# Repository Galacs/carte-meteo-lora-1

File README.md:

# Carte Meteo Lora 1

Solar and battery powered LoRa weather station

## IC List

- STM32L431CCT6 (Low power MCU)
- HT7150 (+3V3 LDO)
- SX1262TR8 (SX1262 LoRa module)
- WS2812B (Addressable RGB LED)
- MS5607 (Pressure sensor)
- GXHT30 (Humidity and temperature sensor)
- HTU21D (Humidity and temperature sensor)
- BQ25798 (1s battery charger with MPPT)
- TPS6282 (SMPS)

## Top preview

## Preview 3d render

## Pictures

## Pin definitions

```c
#define LORA_RST_PIN PB0
#define LORA_DIO1_PIN PB1
#define LORA_BUSY_PIN PB11
#define LORA_DIO3_PIN PB10
#define LORA_CS_PIN PA4
#define LORA_SCK_PIN PA5
#define LORA_MISO_PIN PA6
#define LORA_MOSI PA7

#define BTN_PIN PB12
#define STATUS_PIN PB13

#define SCL_PIN PB6
#define SDA_PIN PB7
#define CE_PIN PA11
#define INT_PIN PA12
#define QON_PIN PA10

#define RGB_PIN PC13

#define RAIN_PIN PB4
#define W_DIR_PIN PA1
#define WIND_PIN PA0
```

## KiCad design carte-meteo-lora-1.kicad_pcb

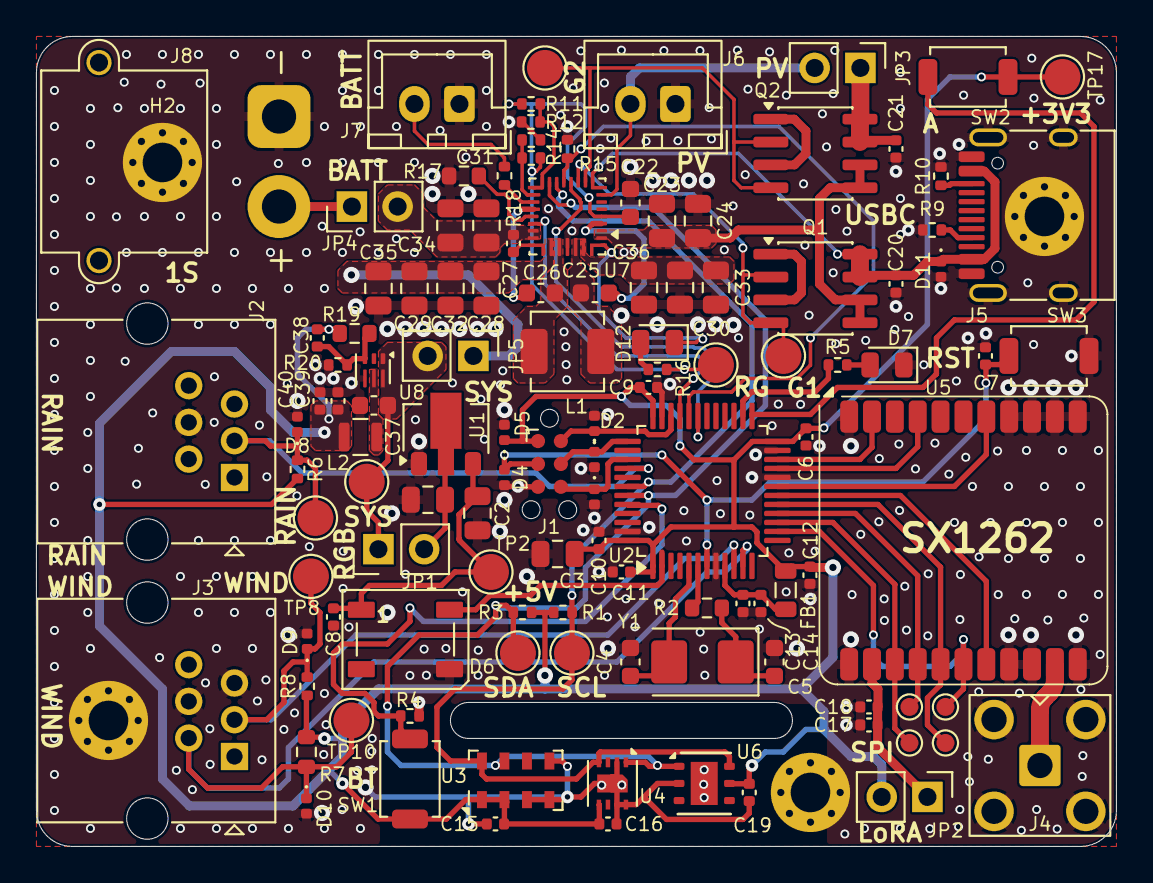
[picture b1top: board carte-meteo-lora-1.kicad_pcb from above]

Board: 2 copper layers, 60.0 x 45.0 mm, 121 parts (0 on the bottom side), 60 nets.

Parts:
C1, C2, C3, C23, C24, C28, C29, C30, C31, C32, C33, C34, C35, C36: 10u; C_0805_2012Metric
C4, C5: 20p; C_0603_1608Metric
C6, C7, C9, C10, C11, C15, C16, C18, C19, C20, C21: 0u1; C_0402_1005Metric
C8, C12, C13: 1u; C_0402_1005Metric
C14: 10n; C_0402_1005Metric
C17, C39, C40: 10u; C_0402_1005Metric
C22: 4u7; C_0603_1608Metric
C25, C26: 47n; C_0603_1608Metric
C27: 1n; C_0402_1005Metric
C37: 10u; C_0603_1608Metric
C38: 100p; C_0402_1005Metric
D1, D2, D3, D4, D5, D8, D9, D10, D11: H5VU10U; Diode_DFN1006
D6: WS2812B; LED_WS2812B_PLCC4_5.0x5.0mm_P3.2mm
D7: YELLOW; LED_0805_2012Metric
D12: GREEN; LED_0805_2012Metric
FB1: 600Ω@100M; L_0805_2012Metric
H1, H2, H3, H4: MountingHole_Pad; MountingHole_2.2mm_M2_Pad_Via
J1: TC2030; Tag-Connect_TC2030-IDC-NL_2x03_P1.27mm_Vertical
J2, J3: Conn_01x04; RJ25_Wayconn_MJEA-660X1_Horizontal
J4: Conn_Coaxial; SMA_BAT_Wireless_BWSMA-KWE-Z001
J5: USB_C_Receptacle_USB2.0_14P; USB_C_Receptacle_HRO_TYPE-C-31-M-12
J6: Solar_Cell; JST_XH_B2B-XH-A_1x02_P2.50mm_Vertical
J7: Conn_01x02; JST_XH_B2B-XH-A_1x02_P2.50mm_Vertical
J8: Battery_Cell; AMASS_XT30PW-M_1x02_P2.50mm_Horizontal
JP1, JP2, JP3, JP4, JP5: Jumper_2_Small_Bridged; PinHeader_1x02_P2.54mm_Vertical
L1: 1u; L_Changjiang_FXL0420
L2: 0u47; TDK_TFM201610ALC
Q1, Q2: AO4882; SOIC-8_3.9x4.9mm_P1.27mm
R1, R3, R4, R6, R8, R11, R12, R15: 10k; R_0402_1005Metric
R2: 560; R_0603_1608Metric
R5, R9, R10, R16: 5k1; R_0402_1005Metric
R7: 470k; R_0603_1608Metric
R13, R20: 100k; R_0402_1005Metric
R14: 52k3; R_0402_1005Metric
R17: 3k; R_0603_1608Metric
R18: 100; R_0402_1005Metric
R19: 430k; R_0603_1608Metric
SW1, SW2, SW3: SW_Push; SW_SPST_TS-1088-xR020
TP1, TP2, TP3, TP4, TP6, TP8, TP10, TP13, TP14, TP15, TP17: TestPoint; TestPoint_Pad_D2.0mm
TP7, TP9, TP11, TP12: TestPoint; TestPoint_Pad_D1.0mm
U1: HT7150-1; SOT-89-3
U2: STM32L431CCTx; LQFP-48_7x7mm_P0.5mm
U3: MS5607-02BA; LGA-8_3x5mm_P1.25mm
U4: GXHT30; Sensirion_DFN-8-1EP_2.5x2.5mm_P0.5mm_EP1.1x1.7mm
U5: SX1262TR8-GC; Silicontra_SX1262ZTR8
U6: HTU21; Texas_PWSON-N6
U7: BQ25798; Texas_RQM0029A_VQFN-29_4x4mm_P0.4mm
U8: TPS6282x; Texas_VSON-6_1.5x1.5mm_P0.5mm_DMQ0006A
Y1: 8M; Crystal_SMD_5032-2Pin_5.0x3.2mm

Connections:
+3V3: C3.1, C6.1, C9.1, C10.1, C11.1, C12.1, C15.2, C16.2, C17.1, C18.2, C19.2, C38.1, C39.1, C40.1, D5.1 (K), FB1.2, J1.1 (VCC), JP2.1 (A), JP2.2 (B), L2.2, R1.2, R3.1, R6.2, R7.1, R8.1, R19.1, SW1.1, SW2.1, TP17.1 (1_1), U2.1 (VBAT), U2.24 (VDD), U2.36 (VDD), U2.48 (VDD), U3.1 (VDD), U3.2 (PS), U4.5 (VDD), U5.13 (VCC), U6.5 (VCC)
+5V: C2.1, C8.1, D6.1 (VDD), TP2.1 (1_1), U1.3 (VOUT)
+REGN: C22.1, R11.1, R13.1, R16.2, TP15.1 (1_1), U7.5 (REGN)
+SYS: C1.1, C28.1, C29.1, C32.1, C35.1, C37.1, JP1.1 (A), JP1.2 (B), JP5.1 (A), JP5.2 (B), TP1.1 (1_1), U1.2 (VIN), U7.25 (SYS), U8.1 (EN), U8.6 (VIN)
+Vbus: C20.1, D11.1 (K), J5.A4 (VBUS), J5.A9 (VBUS), J5.B4 (VBUS), J5.B9 (VBUS), Q1.7 (D1), Q1.8 (D1), U7.9 (VAC1)
/BOOT: R4.2, SW1.2, U2.44 (PH3)
/BTN1: SW2.2, U2.25 (PB12)
/BUSY: U2.22 (PB11), U5.10 (BUSY)
/CS: TP9.1 (1_1), U2.14 (SPI1_NSS), U5.17 (CS)
/DIO1: U2.19 (PB1), U5.5 (DIO1)
/DIO3: U2.21 (PB10), U5.8 (DIO3)
/MISO: TP11.1 (1_1), U2.16 (SPI1_MISO), U5.15 (MISO)
/MOSI: TP12.1 (1_1), U2.17 (SPI1_MOSI), U5.16 (MOSI)
/NRST: C7.2, D4.1 (K), J1.3 (~RESET), SW3.2, U2.7 (NRST)
/Power/~CE: R15.2, U2.32 (PA11), U7.13 (~CE)
/Power/~INT: U2.33 (PA12), U7.21 (~INT)
/Power/~QON: U2.31 (PA10), U7.12 (~QON)
/RAIN: D8.1 (K), J2.3, R6.1, TP6.1 (1_1), U2.40 (PB4)
/RF_LR: J4.1 (In), U5.21 (ANT)
/RGB1: D6.4 (DIN), U2.2 (PC13)
/RST: U2.18 (PB0), U5.18 (RST)
/SCK: TP7.1 (1_1), U2.15 (SPI1_SCK), U5.14 (SCK)
/SCL: R1.1, TP3.1 (1_1), U2.42 (I2C1_SCL), U3.8 (SCLK), U4.4 (SCL), U6.6 (SCL), U7.14 (SCL)
/SDA: R3.2, TP4.1 (1_1), U2.43 (I2C1_SDA), U3.7 (SDI/SDA), U4.1 (SDA), U6.1 (SDA), U7.15 (SDA)
/SWCLK: D3.1 (K), J1.4 (SWCLK), U2.37 (SWCLK)
/SWDIO: D2.1 (K), J1.2 (SWDIO), U2.34 (IR_OUT)
/SWO: D1.1 (K), J1.6 (SWO), U2.39 (SWO)
/WIND: D9.1 (K), J3.3, R8.2, TP8.1 (1_1), U2.10 (PA0)
/W_DIR: D10.1 (K), J3.2, R7.2, TP10.1 (1_1), U2.11 (ADC1_IN6)
/XTAL_I: C4.1, U2.5 (RCC_OSC_IN), Y1.2
/XTAL_O: R2.2, U2.6 (RCC_OSC_OUT)
/XTAL_RO: C5.1, R2.1, Y1.1
GND: C1.2, C2.2, C3.2, C4.2, C5.2, C6.2, C7.1, C8.2, C9.2, C10.2, C11.2, C12.2, C13.2, C14.2, C15.1, C16.1, C17.2, C18.1, C19.1, C20.2, C21.2, C22.2, C23.2, C24.2, C28.2, C29.2, C30.2, C31.2, C32.2, C33.2, C34.2, C35.2, C36.2, C37.2, C39.2, C40.2, D1.2 (A), D2.2 (A), D3.2 (A), D4.2 (A), D5.2 (A), D6.3 (VSS), D7.1 (K), D8.2 (A), D9.2 (A), D10.2 (A), D11.2 (A), H1.1 (1_1), H2.1 (1_1), H3.1 (1_1), H4.1 (1_1), J1.5 (GND), J2.4, J3.4, J3.5, J4.2 (Ext), J5.A1 (GND), J5.A12 (GND), J5.B1 (GND), J5.B12 (GND), J5.SH (SHIELD), J6.1 (+), J7.1, J8.1 (+), R4.1, R9.1, R10.1, R12.1, R14.1, R15.1, R17.2, R20.2, SW3.1, U1.1 (GND), U2.8 (VSSA), U2.20 (PB2), U2.23 (VSS), U2.35 (VSS), U2.47 (VSS), U3.3 (GND), U3.4 (CSB), U3.5 (CSB), U4.2 (ADDR), U4.7 (R), U4.8 (VSS), U4.9 (VSS), U5.1 (GND), U5.2 (GND), U5.3 (GND), U5.4 (GND), U5.11 (GND), U5.12 (GND), U5.19 (GND), U5.20 (GND), U5.22 (GND), U6.2 (GND), U7.27 (GND), U8.4 (GND)
unnamed: C23.1, C24.1, Q1.5 (D2), Q1.6 (D2), Q2.5 (D2), Q2.6 (D2), U7.2 (VBUS), U7.3 (VBUS)
unnamed: D7.2 (A), R5.2
unnamed: D12.2 (A), R16.1
unnamed: D12.1 (K), U7.1 (STAT)
unnamed: J5.A5 (CC1), R9.2
unnamed: J5.B5 (CC2), R10.2
unnamed: C21.1, J6.2 (-), JP3.1 (A), JP3.2 (B), Q2.7 (D1), Q2.8 (D1), U7.8 (VAC2)
unnamed: J7.2, R18.1
unnamed: C27.2, C31.1, C34.1, J8.2 (-), JP4.1 (A), JP4.2 (B), U7.22 (BAT), U7.23 (BAT)
unnamed: Q1.2 (G1), Q1.4 (G2), TP13.1 (1_1), U7.11 (ACDRV1)
unnamed: Q1.1 (S1), Q1.3 (S2)
unnamed: Q2.2 (G1), Q2.4 (G2), TP14.1 (1_1), U7.10 (ACDRV2)
unnamed: Q2.1 (S1), Q2.3 (S2)
unnamed: R5.1, U2.26 (PB13)
unnamed: C13.1, C14.1, FB1.1, U2.9 (VDDA)
unnamed: R18.2, U7.18 (BATP)
unnamed: C25.1, U7.4 (BTST1)
unnamed: C26.1, U7.19 (BTST2)
unnamed: R13.2, R14.2, U7.17 (ILIM_HIZ)
unnamed: C30.1, C33.1, C36.1, U7.29 (PMID)
unnamed: R17.1, U7.20 (PROG)
unnamed: C27.1, U7.24 (SDRV)
unnamed: C25.2, L1.1, U7.28 (SW1)
unnamed: C26.2, L1.2, U7.26 (SW2)
unnamed: R11.2, R12.2, U7.16 (TS)
unnamed: C38.2, R19.2, R20.1, U8.3 (FB)
unnamed: L2.1, U8.5 (SW)

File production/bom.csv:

Designator,Footprint,Quantity,Value,LCSC Part #
"C1, C2, C23, C24, C28, C29, C3, C30, C31, C32, C33, C34, C35, C36",0805,14,10u,C440198
"C10, C11, C15, C16, C18, C19, C20, C21, C6, C7, C9",0402,11,0u1,C307331
"C12, C13, C8",0402,3,1u,C52923
C14,0402,1,10n,C15195
"C17, C39, C40",0402,3,10u,C15525
C22,0603,1,4u7,C19666
"C25, C26",0603,2,47n,C1622
C27,0402,1,1n,C1523
C37,0603,1,10u,C19702
C38,0402,1,100p,C1546
"C4, C5",0603,2,20p,C1648
"D1, D10, D11, D2, D3, D4, D5, D8, D9",Diode_DFN1006,9,H5VU10U,C22395519
D12,0805,1,GREEN,C2297
D6,LED_WS2812B_PLCC4_5.0x5.0mm_P3.2mm,1,WS2812B,C2874885
D7,0805,1,YELLOW,C2296
FB1,0805,1,600Ω@100M,C81034
"J2, J3",RJ25_Wayconn_MJEA-660X1_Horizontal,2,Conn_01x04,C189750
J4,SMA_BAT_Wireless_BWSMA-KWE-Z001,1,Conn_Coaxial,C496551
J5,USB_C_Receptacle_HRO_TYPE-C-31-M-12,1,USB_C_Receptacle_USB2.0_14P,C393939
J6,JST_XH_B2B-XH-A_1x02_P2.50mm_Vertical,1,Solar_Cell,C158012
J7,JST_XH_B2B-XH-A_1x02_P2.50mm_Vertical,1,Conn_01x02,C158012
J8,AMASS_XT30PW-M_1x02_P2.50mm_Horizontal,1,Battery_Cell,C431092
"JP1, JP2, JP3, JP4, JP5",PinHeader_1x02_P2.54mm_Vertical,5,Jumper_2_Small_Bridged,
L1,L_Changjiang_FXL0420,1,1u,C167203
L2,TDK_TFM201610ALC,1,0u47,C2045043
"Q1, Q2",SOIC-8_3.9x4.9mm_P1.27mm,2,AO4882,C3040598
"R1, R11, R12, R15, R3, R4, R6, R8",0402,8,10k,C25744
"R10, R16, R5, R9",0402,4,5k1,C25905
"R13, R20",0402,2,100k,C25741
R14,0402,1,52k3,C26982
R17,0603,1,3k,C4211
R18,0402,1,100,C25076
R19,0603,1,430k,C25969
R2,0603,1,560,C23204
R7,0603,1,470k,C23178
"SW1, SW2, SW3",SW_SPST_TS-1088-xR020,3,SW_Push,C720477
TP4,TestPoint_Pad_D2.0mm,1,TestPoint,
U1,SOT-89-3,1,HT7150-1,C347184
U2,LQFP-48_7x7mm_P0.5mm,1,STM32L431CCTx,C486681
U3,LGA-8_3x5mm_P1.25mm,1,MS5607-02BA,C97627
U4,Sensirion_DFN-8-1EP_2.5x2.5mm_P0.5mm_EP1.1x1.7mm,1,GXHT30,C2913569
U5,Silicontra_SX1262ZTR8,1,SX1262TR8-GC,C42381682
U6,Texas_PWSON-N6,1,HTU21,C83479
U7,Texas_RQM0029A_VQFN-29_4x4mm_P0.4mm,1,BQ25798,C2876593
U8,Texas_VSON-6_1.5x1.5mm_P0.5mm_DMQ0006A,1,TPS6282x,C2650334
Y1,Crystal_SMD_5032-2Pin_5.0x3.2mm,1,8M,C115962

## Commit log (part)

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2026-05-19 remove TMP117 temp sensor
2026-05-19 schem: add MS5607 Pressure sensor
2026-05-20 schem: remove old gpios
2026-05-20 schem: add esp32-c5 with decoupling caps
2026-05-20 schem: replace esp32-s3 with esp32-c5
2026-05-20 schem: add GXHT30 humidity and temperature sensor
2026-05-20 schem: add HTU21 humidity and temperature
2026-05-20 schem: add wind and rain connectors
2026-05-20 schem: add SX1262 based lora module
2026-05-21 schem: add ordering info to BOM
2026-05-21 schem: fix BOM
2026-05-24 schem: add esp rf matching networks
2026-05-24 schem: reorganize
2026-05-24 schem: add TPS62933 5V SMPS
2026-05-24 schem: rf fix switchable connectors orientation
2026-05-24 schem: fix VDD_SPI cap
2026-05-24 schem: improve rain and wind connectors
2026-05-24 schem: add rain/wind schmitt trigger
2026-05-25 schem: remove 3s BMS
2026-05-25 schem: add BQ25798 MPPT/Charger/Protection/Boost
2026-05-25 schem: add TPS6282 3.3v SMPS
2026-05-25 schem: remove esp32
2026-05-25 schem: add STM32F103C8Tx
2026-05-25 schem: add usbc pwer connector
2026-05-25 schem: remove oled display
2026-05-25 schem: add HT7150-1 5V LDO for rgb led
2026-05-25 schem: connect gpios
2026-05-26 schem: change mcu to stm32l4
2026-05-26 schem: connect gpios to mcu
2026-05-26 schem: add current measure jumpers
2026-05-26 schem: add no connects
2026-05-26 schem: add test points
2026-05-26 schem: run and fix ERC
2026-05-26 schem: add net classes
2026-05-26 schem: assign footprints
2026-05-26 schem: add title
2026-05-26 schem: renumber
2026-05-26 pcb: import jlc 2 layer stackup
2026-05-26 pcb: add missing 3d models
2026-05-27 pcb: initial partitioning
2026-05-29 schem: add title to other sheet
2026-05-29 pcb: add missing lora 3d model
2026-05-29 pcb: add usb layout
2026-05-29 pcb: add solar charger layout
2026-05-29 pcb: add rgb led routing
2026-05-29 pcb: add smps routing
2026-05-29 pcb: add wind/rain connectors layout
2026-05-29 pcb: add sensors layout
2026-05-29 pcb: add lora layout
2026-05-29 pcb: add stm32 layout
2026-05-29 pcb: add board outline and final placement
2026-05-29 schem: add mounting holes
2026-05-29 pcb: add gnd planes
2026-05-29 pcb: add gnd vias
2026-05-29 pcb: add grid/place origin
2026-05-29 pcb: reorganize programmable gpios
2026-05-29 pcb: add rf routing
2026-05-29 pcb: add xtal routing
2026-05-29 pcb: add swd routing
2026-05-29 pcb: add i2c routing
2026-05-29 pcb: add solar charger routing
2026-05-29 pcb: add lora spi routing
2026-05-29 pcb: add rain/wind connectors routing
2026-05-29 pcb: add smps and +5v pwr routing
2026-05-29 pcb: add lora gpio routing
2026-05-29 pcb: add boot/rst routing
2026-05-29 pcb: connect charger to mcu
2026-05-29 pcb: add +3v3 pwr routing
2026-05-30 pcb: add missing connections
2026-05-30 pcb: add stitching vias
2026-05-30 pcb(silk): clean designators
2026-05-30 pcb: add temp sensors thermal pads
2026-05-30 pcb(silk): add user txt
2026-05-30 pcb: add title
2026-05-30 generate production files
2026-06-08 docs: add pin definitions
